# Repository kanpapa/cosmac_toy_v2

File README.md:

# COSMAC Toy Computer Version 2

[COSMAC Toy Computer](https://github.com/kanpapa/cosmac_toy)は「トラ技別冊 つくるシリーズ7 手作りコンピュータ入門」（1981年5月初版）を参考にして、COSMAC CPUボードやプログラムローダーや実験回路をコンパクトな基板にまとめて製作したものです。  
ROMは搭載されておらず、トグルスイッチでRAMにプログラムを書き込んで実行できます。  
16進キーボードを使ったことはあるけど、トグルスイッチを使ってプログラムを動かしてみたいという方の願いを叶えようという思いで作られたシンプルなボードです。モニタプログラムなどの助けを借りずに、トグルスイッチでメモリを直接書き換えてプログラムを実行するといった一連の操作を体験できます。

最初に製作したCOSMAC TOYは1980年代の当時の環境に近づけるべく可能な限り書籍を忠実に再現することを第一に製作しましたので、やや入手が容易ではないパーツも含まれていました。  
このため、実機を使って[COSMACマイコン](https://kanpapa.com/cosmac/cosmac-cpu)の基本的な動きとトグルスイッチによるブートストラップを容易に体験いただけるようにVersion 2として見直しを行いました。

さらに高度なプログラミングを行いたい場合は、モニタが搭載された[SBC1802](https://vintagechips.wordpress.com/2021/04/13/sbc1802fixed/)や[MemberShip Card](https://www.sunrise-ev.com/1802.htm)などの利用をおすすめします。

## Version 2での変更点

* CPUボードとローダーボードを1枚の基板にまとめ、さらに製作を容易にしました。
* メモリを書き込み禁止にするトグルスイッチを追加することで、メモリ内容の読み出しや正しく手順を踏めばメモリの修正も行えるようになりました。
* 600milのS-RAMを使用できるようにしました。これにより600milの6264ALPやDIP変換基板に実装したフラットパッケージのS-RAMも使用できます。
* COSMAC CPUの全ピンにアクセスできるようにピンソケット用のパターンを併設しました。
* Q出力がLEDでモニタできるようになりました。基板単体でQ出力の確認ができます。
* COSMAC CPUとS-RAMを除きすべて秋月電子さんで購入できるパーツとしました。
* USB-C電源コネクタを追加しました。(Rev.0.3)
* 入力トグルスイッチと出力LEDにおいて上位4ビットと下位4ビットの間隔を少し空けました。(Rev.0.3)

## スペック

* CPU: COSMAC CDP1802
* RAM: 256byte
* ROM: 無し
* CLOCK: 約400kHz
* I/O: バスLED, Q-LED, バス設定トグルスイッチ, モード設定トグルスイッチ
* 電源: 5V 標準DCジャック(センタープラス)、USB-C電源(Rev.0.3)
* メモリバックアップバッテリー: CR2032 3V
* サイズ: 95mmX72mm
* 重さ: 約89g（全パーツ実装時）

## 外観
Rev.0.3  
  
[Rev.0.2](/docs/images/cosmac_toy_v2-rev02-600mil.jpg)  
[Rev.0.1](/docs/images/cosmac_toy_v2-rev01-prototype.jpg)  

## 特徴

* 入手が容易なパーツを使い、回路を極力簡素化することで必要なパーツ数を減らしています。専用基板も表面実装パーツは使用せずに製作しやすくしています。
* トグルスイッチで直接メモリに書き込むため、ROMライタなどの開発ツールは不要です。
* COSMAC CPUの全ピンにアクセスできるようにピンソケットを併設しています。CPUバスやQ出力やEF1~4入力などのアクセスはここから行ってください。
* メモリは6264を使用していますが、実際に使えるのは256バイトだけです。これはトグルスイッチで正確に手入力できるのは256バイトが限界と思われるため、アドレスバスを簡略化したためです。
* S-RAMは簡易的なバッテリバックアップが行えます。SW11をSTBYにするとメモリをスタンバイ状態にし、バッテリーで内容が保持されます。
* 8つのLEDはバスの信号をラッチしてバスの状態を表示することができます。
* 右上の3つのトグルスイッチで、CPUの動作モードを設定したあとに、DMA INにつながっているプッシュスイッチを押すことで、トグルスイッチで設定した値をメモリに書き込むことができます。ROにすることでメモリに書き込まずメモリの状態を確認することもできます。
* トグルスイッチはバスの信号を直接0/1に設定します。通常はバスバッファを介しますが、シンプルな回路にするために省略しています。
* Q出力はLEDが接続されています。  
* COSMAC CPUのクロックはCR発振なのでCRの値を変えることで周波数を調整できます。
* 本基板のサイズは秋月電子のB基板に合わせました。

## 基本的な操作方法

* [Quick start guide](/docs/cosmac_toy_v2_quick_start_guide.pdf)も合わせてご覧ください。

    UP    トグルスイッチを上側に倒します  
    DOWN  トグルスイッチを下側に倒します  
     ↓  　トグルスイッチの状態をそのまま維持します。（変更しない）  
     ー   トグルスイッチの状態は任意です。（上側でも下側でも良い）  

1. メモリ書き込み

    |Step|SW9|SW10|SW12|操作内容|
    |---|----|---|----|----|
    |1	|UP|DOWN|-|CPUを初期状態(P, X, R(0)を0)にする(RESETモード)|	
    |2	|↓|↓|UP|メモリ書き込み許可|
    |3	|DOWN|↓|↓|メモリロード状態にする(LOADモード)|
    |4	|| | |トグルスイッチでメモリに書き込む値を設定→DMAINを押す（これを繰り返す） |

1. メモリ読み出し
    |Step|SW9|SW10|SW12|操作内容|
    |---|---|----|----|----|
    |1	|UP|DOWN|-|CPUを初期状態にする(RESETモード)|
    |2  |↓|↓|DOWN|メモリ書き込み禁止|
	|3  |DOWN|↓|↓|メモリロード状態にする(LOADモード)|	
	|4  | | | |DMAINボタンを押すとメモリの内容が表示される（これを繰り返す）|		

1. プログラム実行
    |Step|SW9|SW10|SW12|操作内容|
    |---|----|---|----|----|
    |1|UP|DOWN|-|CPUを初期状態にする(RESETモード)|
    |2|↓|↓|UP|メモリ書き込み許可(メモリに書き込む処理があるプログラムの場合)|	
	|3|↓|UP|↓|プログラム実行状態にする(RUNモード)|

1. プログラム一時停止
    |Step|SW9|SW10|SW12|操作内容|
    |---|---|---|---|---|
	|1|DOWN|UP|-|プログラム実行を一時停止する(PAUSEモード)|
	|2|UP|↓|- |プログラム実行状態にする(RUNモード)|

1. メモリバックアップ状態〜通常状態への切替
    |Step|SW9|SW10|SW12|SW11|操作内容|
    |---|---|---|---|---|---|
    |1|DOWN|UP|-|RUN|プログラムを一時停止する(PAUSEモード)|
    |2|↓|↓|DOWN|↓|メモリ書き込み禁止|
    |3|↓|↓|↓|STBY|RAMをスタンバイモードにする|
    |4|↓|↓|↓|↓|電源を切断|
    |5|DOWN|UP|DOWN|STBY|PAUSEモード+メモリ書き込み禁止になっていることを確認|
    |6|↓|↓|↓|↓|電源を投入|
    |7|↓|↓|↓|RUN|RAMをノーマルモードにする|

※メモリバックアップを行わない場合はリチウム電池は抜いておいてください。電源が供給されない状態でSW11がRUNのままだと放電してしまいます。

## ハードウェア

- [回路図](/schematics/)
- [部品表](/bom/)
- [KiCadデータ](/kicad/)
- [ガーバーデータ](/gerber/)
- [組み立て手順例](/docs/Assembly_instruction/)
- 組み立て時の注意事項  
    - 部品表に記載されているLEDと異なるLEDを使用する場合は、RN3 2.2KΩの集合抵抗では眩しすぎる場合もありますので、丸ピンソケットを利用して集合抵抗を交換調整できるようにしておくことをお勧めします。

## ソフトウェア
 
- [サンプルアプリケーション](/programs/)

## 補足情報

- [COSMAC研究会](https://kanpapa.com/cosmac/)に関連記事をまとめています。

## 参考・引用文献

- トランジスタ技術別冊 つくるシリーズ７ 手作りコンピュータ入門 CQ出版社, 1981
- [KiCad 8 入門実習テキスト『KiCad Basics for 8.0』Kosaka.Lab.出版掛](https://kosakalab.booth.pm/items/5554691)
- [intersil CDP1802AC/3データシート](https://www.renesas.com/jp/ja/www/doc/datasheet/cdp1802ac-3.pdf)
- [SB-Assembler](https://www.sbprojects.net/sbasm/)
- [COSMAC ELF - RCA CDP1802 Computing](http://www.cosmacelf.com/)
- [Compute II Issue 3: The 1802 Instruction Set](https://www.atarimagazines.com/computeii/issue3/page52.php)
- [The 1802 Membership Card](http://www.sunrise-ev.com/1802.htm)

## 利用上の注意

本サイトに掲載している回路、技術、プログラムなどは無保証です。  
これらの利用によって発生したトラブルには責任を負いかねます。自己責任にてご利用ください。  
KiCADデータおよびガーバーデータはCC BY-SA 4.0 (Copyright (C) 2024 Kazuhiro Ouchi)です。  
サンプルプログラムはMITライセンスです。

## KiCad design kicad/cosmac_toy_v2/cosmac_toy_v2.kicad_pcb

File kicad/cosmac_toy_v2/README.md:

# COSMAC TOY V2 KiCad project

COSMAC TOY V2の基板のKiCADデータです。

以下に公開されているフットプリントを使用させていただきました。

* USB Type-Cコネクター 電源供給用	A295-CTRPB-1:A295-CTRPB-1  
https://github.com/21km43/A295-CTRPB-1_KiCAD  
Copyright (c) 2023 Koki Mizumoto

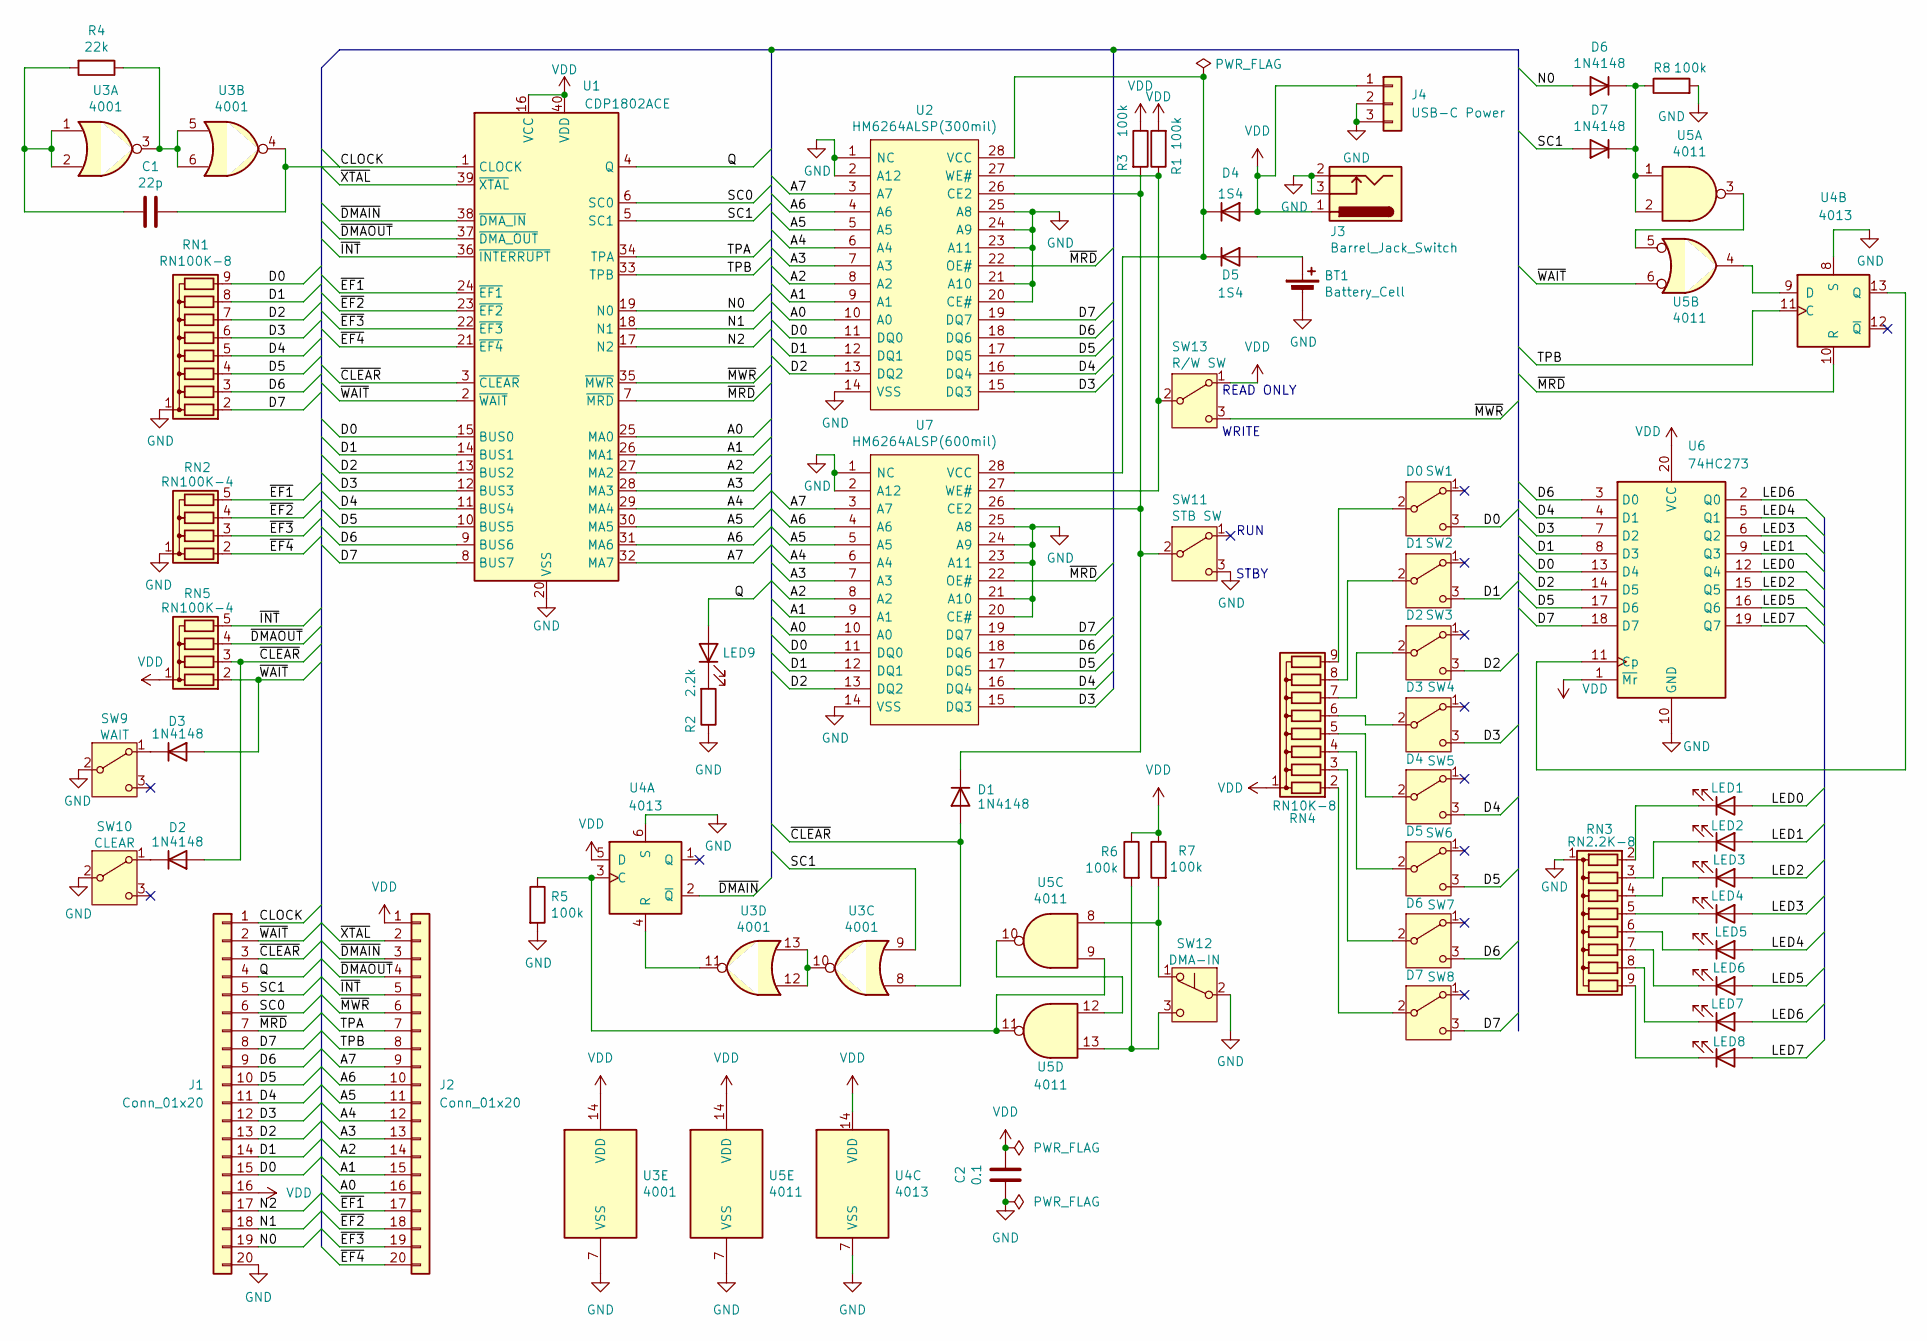
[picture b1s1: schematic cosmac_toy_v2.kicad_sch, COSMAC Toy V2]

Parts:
BT1: Battery_Cell; CH243-2032CF
C1: 22p; C_Disc_D4.7mm_W2.5mm_P5.00mm
C2: 0.1; C_Disc_D4.7mm_W2.5mm_P5.00mm
D1, D2, D3, D6, D7: 1N4148; D_DO-35_SOD27_P7.62mm_Horizontal
D4, D5: 1S4; D_A-405_P7.62mm_Horizontal
J1, J2: Conn_01x20; PinSocket_1x20_P2.54mm_Vertical
J3: Barrel_Jack_Switch; BarrelJack_Horizontal
J4: USB-C Power; A295-CTRPB-1
LED1, LED2, LED3, LED4, LED5, LED6, LED7, LED8: DATA_LED; LED_D3.0mm
LED9: Q; LED_D3.0mm
R1, R3, R5, R6, R7, R8: 100k; R_Axial_DIN0207_L6.3mm_D2.5mm_P7.62mm_Horizontal
R2: 2.2k; R_Axial_DIN0207_L6.3mm_D2.5mm_P7.62mm_Horizontal
R4: 22k; R_Axial_DIN0207_L6.3mm_D2.5mm_P7.62mm_Horizontal
RN1: RN100K-8; R_Array_SIP9
RN2, RN5: RN100K-4; R_Array_SIP5
RN3: RN2.2K-8; R_Array_SIP9
RN4: RN10K-8; R_Array_SIP9
SW1: D0; SW_Toggle_P2.54mm_Vertical
SW2: D1; SW_Toggle_P2.54mm_Vertical
SW3: D2; SW_Toggle_P2.54mm_Vertical
SW4: D3; SW_Toggle_P2.54mm_Vertical
SW5: D4; SW_Toggle_P2.54mm_Vertical
SW6: D5; SW_Toggle_P2.54mm_Vertical
SW7: D6; SW_Toggle_P2.54mm_Vertical
SW8: D7; SW_Toggle_P2.54mm_Vertical
SW9: WAIT; SW_Toggle_P2.54mm_Vertical
SW10: CLEAR; SW_Toggle_P2.54mm_Vertical
SW11: STB SW; PinHeader_1x03_P2.54mm_Vertical
SW12: DMA-IN; PushSwitch
SW13: R/W SW; SW_Toggle_P2.54mm_Vertical
U1: CDP1802ACE; DIP-40_W15.24mm_Socket
U2: HM6264ALSP(300mil); DIP-28_W7.62mm_Socket
U3: 4001; DIP-14_W7.62mm
U4: 4013; DIP-14_W7.62mm
U5: 4011; DIP-14_W7.62mm
U6: 74HC273; DIP-20_W7.62mm
U7: HM6264ALSP(600mil); DIP-28_W15.24mm_Socket

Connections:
/A0: J2.16, U1.25 (MA0), U2.10 (A0), U7.10 (A0)
/A1: J2.15, U1.26 (MA1), U2.9 (A1), U7.9 (A1)
/A2: J2.14, U1.27 (MA2), U2.8 (A2), U7.8 (A2)
/A3: J2.13, U1.28 (MA3), U2.7 (A3), U7.7 (A3)
/A4: J2.12, U1.29 (MA4), U2.6 (A4), U7.6 (A4)
/A5: J2.11, U1.30 (MA5), U2.5 (A5), U7.5 (A5)
/A6: J2.10, U1.31 (MA6), U2.4 (A6), U7.4 (A6)
/A7: J2.9, U1.32 (MA7), U2.3 (A7), U7.3 (A7)
/CLOCK: C1.2, J1.1, U1.1 (CLOCK), U3.4
/D0: J1.15, RN1.9 (R8), SW1.3 (C), U1.15 (BUS0), U2.11 (DQ0), U6.13 (D4), U7.11 (DQ0)
/D1: J1.14, RN1.8 (R7), SW2.3 (C), U1.14 (BUS1), U2.12 (DQ1), U6.8 (D3), U7.12 (DQ1)
/D2: J1.13, RN1.7 (R6), SW3.3 (C), U1.13 (BUS2), U2.13 (DQ2), U6.14 (D5), U7.13 (DQ2)
/D3: J1.12, RN1.6 (R5), SW4.3 (C), U1.12 (BUS3), U2.15 (DQ3), U6.7 (D2), U7.15 (DQ3)
/D4: J1.11, RN1.5 (R4), SW5.3 (C), U1.11 (BUS4), U2.16 (DQ4), U6.4 (D1), U7.16 (DQ4)
/D5: J1.10, RN1.4 (R3), SW6.3 (C), U1.10 (BUS5), U2.17 (DQ5), U6.17 (D6), U7.17 (DQ5)
/D6: J1.9, RN1.3 (R2), SW7.3 (C), U1.9 (BUS6), U2.18 (DQ6), U6.3 (D0), U7.18 (DQ6)
/D7: J1.8, RN1.2 (R1), SW8.3 (C), U1.8 (BUS7), U2.19 (DQ7), U6.18 (D7), U7.19 (DQ7)
/LED0: LED1.2 (A), U6.12 (Q4)
/LED1: LED2.2 (A), U6.9 (Q3)
/LED2: LED3.2 (A), U6.15 (Q5)
/LED3: LED4.2 (A), U6.6 (Q2)
/LED4: LED5.2 (A), U6.5 (Q1)
/LED5: LED6.2 (A), U6.16 (Q6)
/LED6: LED7.2 (A), U6.2 (Q0)
/LED7: LED8.2 (A), U6.19 (Q7)
/N0: D6.2 (A), J1.19, U1.19 (N0)
/N1: J1.18, U1.18 (N1)
/N2: J1.17, U1.17 (N2)
/Q: J1.4, LED9.2 (A), U1.4 (Q)
/SC0: J1.6, U1.6 (SC0)
/SC1: D7.2 (A), J1.5, U1.5 (SC1), U3.9
/TPA: J2.7, U1.34 (TPA)
/TPB: J2.8, U1.33 (TPB), U4.11 (C)
/~CLEAR: D1.2 (A), D2.2 (A), J1.3, RN5.3 (R2), U1.3 (~CLEAR), U3.8
/~DMAIN: J2.3, U1.38 (~DMA_IN), U4.2 (~Q)
/~DMAOUT: J2.4, RN5.4 (R3), U1.37 (~DMA_OUT)
/~EF1: J2.17, RN2.5 (R4), U1.24 (~EF1)
/~EF2: J2.18, RN2.4 (R3), U1.23 (~EF2)
/~EF3: J2.19, RN2.3 (R2), U1.22 (~EF3)
/~EF4: J2.20, RN2.2 (R1), U1.21 (~EF4)
/~INT: J2.5, RN5.5 (R4), U1.36 (~INTERRUPT)
/~MRD: J1.7, U1.7 (~MRD), U2.22 (OE#), U4.10 (R), U7.22 (OE#)
/~MWR: J2.6, SW13.3 (C), U1.35 (~MWR)
/~WAIT: D3.2 (A), J1.2, RN5.2 (R1), U1.2 (~WAIT), U5.6
/~XTAL: J2.2, U1.39 (~XTAL)
GND: BT1.2 (-), C2.2, J1.20, J3.2, J3.3, J4.2, J4.3, R2.1, R5.2, R8.2, RN1.1 (common), RN2.1 (common), RN3.1 (common), SW9.2 (B), SW10.2 (B), SW11.3 (C), SW12.2 (B), U1.20 (VSS), U2.1 (NC), U2.2 (A12), U2.14 (VSS), U2.20 (CE#), U2.21 (A10), U2.23 (A11), U2.24 (A9), U2.25 (A8), U3.7 (VSS), U4.6 (S), U4.7 (VSS), U4.8 (S), U5.7 (VSS), U6.10 (GND), U7.1 (NC), U7.2 (A12), U7.14 (VSS), U7.20 (CE#), U7.21 (A10), U7.23 (A11), U7.24 (A9), U7.25 (A8)
unnamed: BT1.1 (+), D5.2 (A)
unnamed: C1.1, R4.2, U3.1, U3.2
unnamed: D1.1 (K), R3.2, SW11.2 (B), U2.26 (CE2), U7.26 (CE2)
unnamed: D2.1 (K), SW10.1 (A)
unnamed: D3.1 (K), SW9.1 (A)
unnamed: D4.1 (K), D5.1 (K), U2.28 (VCC), U7.28 (VCC)
unnamed: D6.1 (K), D7.1 (K), R8.1, U5.1, U5.2
unnamed: LED1.1 (K), RN3.2 (R1)
unnamed: LED2.1 (K), RN3.3 (R2)
unnamed: LED3.1 (K), RN3.4 (R3)
unnamed: LED4.1 (K), RN3.5 (R4)
unnamed: LED5.1 (K), RN3.6 (R5)
unnamed: LED6.1 (K), RN3.7 (R6)
unnamed: LED7.1 (K), RN3.8 (R7)
unnamed: LED8.1 (K), RN3.9 (R8)
unnamed: LED9.1 (K), R2.2
unnamed: R4.1, U3.3, U3.5, U3.6
unnamed: RN4.2 (R1), SW8.2 (B)
unnamed: RN4.3 (R2), SW7.2 (B)
unnamed: RN4.4 (R3), SW6.2 (B)
unnamed: RN4.5 (R4), SW5.2 (B)
unnamed: RN4.6 (R5), SW4.2 (B)
unnamed: RN4.7 (R6), SW3.2 (B)
unnamed: RN4.8 (R7), SW2.2 (B)
unnamed: RN4.9 (R8), SW1.2 (B)
unnamed: R7.2, SW12.1 (A), U5.8
unnamed: R6.2, SW12.3 (C), U5.13
unnamed: R1.1, SW13.2 (B), U2.27 (WE#), U7.27 (WE#)
unnamed: U3.10, U3.12, U3.13
unnamed: R5.1, U4.3 (C), U5.9, U5.11
unnamed: U3.11, U4.4 (R)
unnamed: U4.9 (D), U5.4
unnamed: U4.13 (Q), U6.11 (Cp)
unnamed: U5.3, U5.5
unnamed: U5.10, U5.12
VDD: C2.1, D4.2 (A), J1.16, J2.1, J3.1, J4.1, R1.2, R3.1, R6.1, R7.1, RN4.1 (common), RN5.1 (common), SW13.1 (A), U1.16 (VCC), U1.40 (VDD), U3.14 (VDD), U4.5 (D), U4.14 (VDD), U5.14 (VDD), U6.1 (~Mr), U6.20 (VCC)

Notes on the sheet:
RUN
STBY
WRITE
READ ONLY

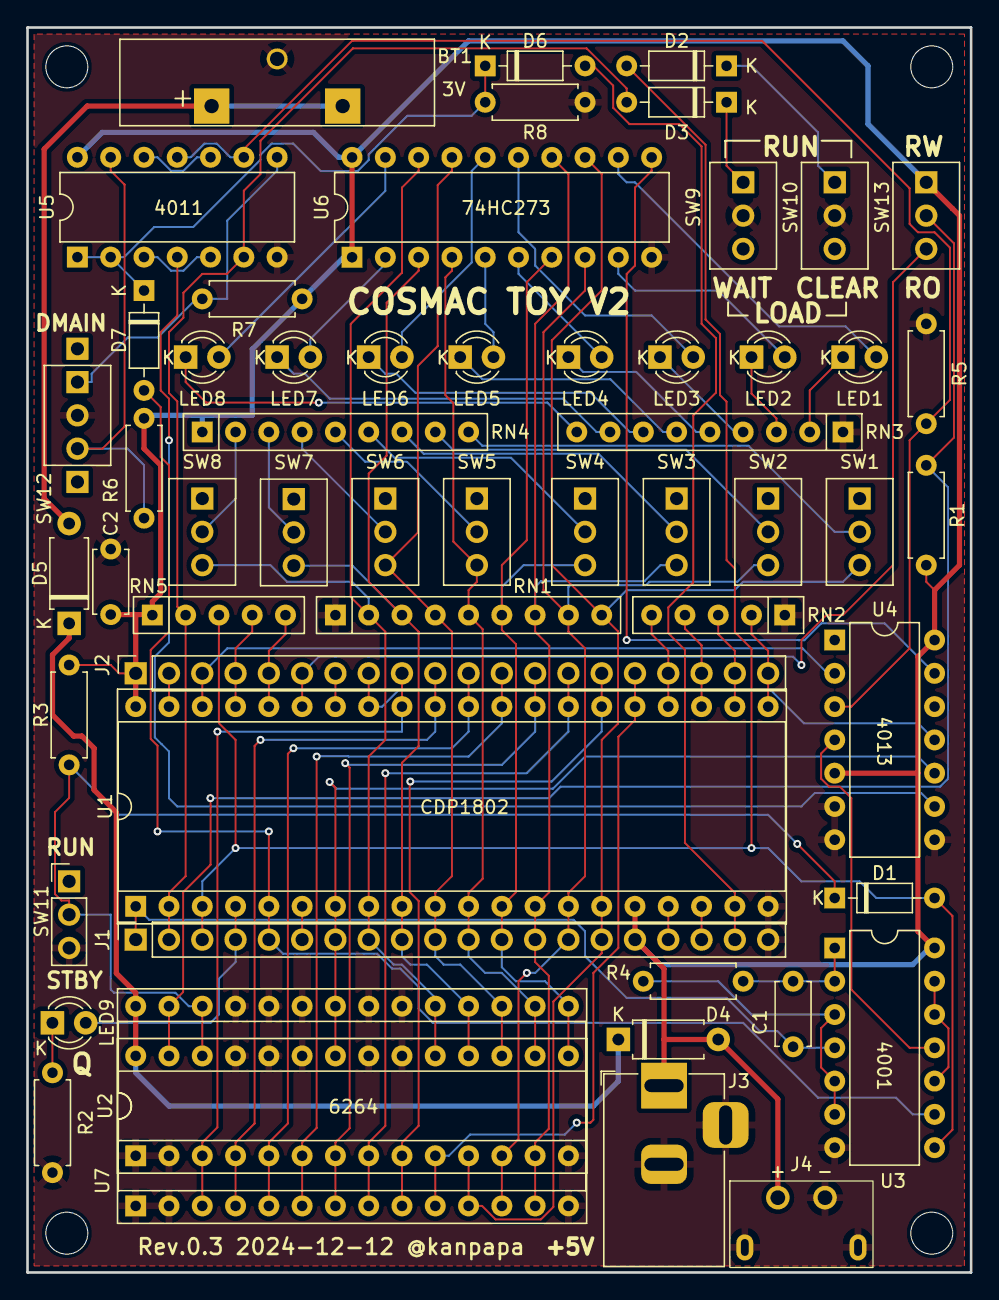
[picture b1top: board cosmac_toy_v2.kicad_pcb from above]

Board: 2 copper layers, 72.0 x 95.0 mm, 60 parts (0 on the bottom side), 82 nets.

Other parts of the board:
MH1, MH2, MH3, MH4: MountingHole_3.2mm_M3

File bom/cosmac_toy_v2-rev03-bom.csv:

Reference,Value,Datasheet,Footprint,Qty,参考入手先,秋月電子販売コード,参考価格,計,
BT1,Battery_Cell,ボタン電池基板取付用ホルダー CR2032用(縦型),Switch_Toggle:CH243-2032CF,1,秋月電子,102019,80,80,
C1,22p,積層セラミックコンデンサー 22pF50V C0G 5mm,Capacitor_THT:C_Disc_D4.7mm_W2.5mm_P5.00mm,1,秋月電子,108094,130,13,10個入
C2,0.1uF,積層セラミックコンデンサー 0.1μF100V X7R 5mmピッチ,Capacitor_THT:C_Disc_D4.7mm_W2.5mm_P5.00mm,1,秋月電子,115927,120,12,10個入
"D1,D2,D3,D6,D7",1N4148,汎用小信号高速スイッチング・ダイオード 1N4148 100V200mA,Diode_THT:D_DO-35_SOD27_P7.62mm_Horizontal,5,秋月電子,100941,150,15,50本入り
"D4,D5",1S4,整流用ショットキーダイオード 40V1A 1S4,Diode_THT:D_A-405_P7.62mm_Horizontal,2,秋月電子,100127,20,40,
"J1,J2",Conn_01x20,ピンソケット (メス) 1×20 (20P),Connector_PinSocket_2.54mm:PinSocket_1x20_P2.54mm_Vertical,2,秋月電子,103077,50,100,
J3,Barrel_Jack_Switch,2.1mm標準DCジャック(4A) 基板取付用 MJ-179PH,Connector_BarrelJack:BarrelJack_Horizontal,1,秋月電子,106568,40,40,J3とJ4はどちらかを選択
J4,USB-C Power,USB Type-Cコネクター 電源供給用,A295-CTRPB-1:A295-CTRPB-1,1,秋月電子,116895,40,40,https://github.com/21km43/A295-CTRPB-1_KiCAD
"LED1,LED2,LED3,LED4,LED5,LED6,LED7,LED8",DATA_LED,3mm赤色LED 625nm 70度 OSR5JA3Z74A,LED_THT:LED_D3.0mm,8,秋月電子,111577,10,80,10個入
LED9,Q,3mm赤色LED 625nm 70度 OSR5JA3Z74A,LED_THT:LED_D3.0mm,1,秋月電子,111577,10,10,
"R1,R3,R5,R6,R7,R8",100k,カーボン抵抗(炭素皮膜抵抗) 1/4W100kΩ,Resistor_THT:R_Axial_DIN0207_L6.3mm_D2.5mm_P7.62mm_Horizontal,6,秋月電子,125104,130,7.8,100本入
R4,22k,カーボン抵抗(炭素皮膜抵抗) 1/4W22kΩ,Resistor_THT:R_Axial_DIN0207_L6.3mm_D2.5mm_P7.62mm_Horizontal,1,秋月電子,125223,130,1,
R2,2.2k,カーボン抵抗(炭素皮膜抵抗) 1/4W2.2kΩ,Resistor_THT:R_Axial_DIN0207_L6.3mm_D2.5mm_P7.62mm_Horizontal,1,秋月電子,125222,100,1,100本入
RN1,RN100K-8,集合抵抗 8素子 100kΩ,Resistor_THT:R_Array_SIP9,1,秋月電子,114228,25,25,
RN2,RN100K-4,集合抵抗 4素子 100kΩ,Resistor_THT:R_Array_SIP5,1,秋月電子,114246,15,15,
RN3,RN2.2K-8,集合抵抗 8素子 2.2kΩ,Resistor_THT:R_Array_SIP9,1,秋月電子,113915,30,30,
RN4,RN10K-8,集合抵抗 8素子 10kΩ,Resistor_THT:R_Array_SIP9,1,秋月電子,111910,40,40,
RN5,RN100K-4,集合抵抗 4素子 100kΩ,Resistor_THT:R_Array_SIP5,1,秋月電子,114246,15,15,
SW1,D0,基板用小型3Pトグルスイッチ 1回路2接点,Switch_Toggle:SW_Toggle_P2.54mm_Vertical,1,秋月電子,102399,130,130,
SW2,D1,基板用小型3Pトグルスイッチ 1回路2接点,Switch_Toggle:SW_Toggle_P2.54mm_Vertical,1,秋月電子,102399,130,130,
SW3,D2,基板用小型3Pトグルスイッチ 1回路2接点,Switch_Toggle:SW_Toggle_P2.54mm_Vertical,1,秋月電子,102399,130,130,
SW4,D3,基板用小型3Pトグルスイッチ 1回路2接点,Switch_Toggle:SW_Toggle_P2.54mm_Vertical,1,秋月電子,102399,130,130,
SW5,D4,基板用小型3Pトグルスイッチ 1回路2接点,Switch_Toggle:SW_Toggle_P2.54mm_Vertical,1,秋月電子,102399,130,130,
SW6,D5,基板用小型3Pトグルスイッチ 1回路2接点,Switch_Toggle:SW_Toggle_P2.54mm_Vertical,1,秋月電子,102399,130,130,
SW7,D6,基板用小型3Pトグルスイッチ 1回路2接点,Switch_Toggle:SW_Toggle_P2.54mm_Vertical,1,秋月電子,102399,130,130,
SW8,D7,基板用小型3Pトグルスイッチ 1回路2接点,Switch_Toggle:SW_Toggle_P2.54mm_Vertical,1,秋月電子,102399,130,130,
SW9,WAIT,基板用小型3Pトグルスイッチ 1回路2接点,Switch_Toggle:SW_Toggle_P2.54mm_Vertical,1,秋月電子,102399,130,130,
SW10,CLEAR,基板用小型3Pトグルスイッチ 1回路2接点,Switch_Toggle:SW_Toggle_P2.54mm_Vertical,1,秋月電子,102399,130,130,
SW11,STB SW,スライドスイッチ 1回路2接点 基板用,Connector_PinHeader_2.54mm:PinHeader_1x03_P2.54mm_Vertical,1,秋月電子,115707,20,20,
SW12,DMA-IN,押しボタンスイッチ(赤),Switch_Toggle:PushSwitch,1,秋月電子,104366,180,180,
SW13,R/W SW,基板用小型3Pトグルスイッチ 1回路2接点,Switch_Toggle:SW_Toggle_P2.54mm_Vertical,1,秋月電子,102399,130,130,
U1,CDP1802ACE,http://www.cosmacelf.com/publications/data-sheets/cdp1802.pdf,Package_DIP:DIP-40_W15.24mm_Socket,1,オレンジピコ,,746,746,
U2,HM6264ALSP(300mil),,Package_DIP:DIP-28_W7.62mm_Socket,1,ー,,,,U2とU7はどちらかを選択
U3,4001,4回路2入力NOR TC4001BP,Package_DIP:DIP-14_W7.62mm,1,秋月電子,110911,50,50,
U4,4013,2回路Dフリップフロップ TC4013BP,Package_DIP:DIP-14_W7.62mm,1,秋月電子,114210,40,40,
U5,4011,4回路2入力NAND TC4011BP,Package_DIP:DIP-14_W7.62mm,1,秋月電子,113729,40,40,
U6,74HC273,Dフリップフロップ(D-FF) TC74HC273AP,Package_DIP:DIP-20_W7.62mm,1,秋月電子,115412,70,70,
U7,HM6264ALP(600mil),,Package_DIP:DIP-28_W15.24mm_Socket,1,若松通商,,850,850,U2とU7はどちらかを選択
,,専用基板,,1,JLCPCB,,100,100,5枚で約500円
,,丸ピンICソケット (40P),,1,秋月電子,100034,90,90,
,,丸ピンICソケット (28P) 300mil,,1,秋月電子,101339,70,70,
,,ICソケット (20P),,1,秋月電子,100009,170,17,10個入
,,ICソケット (14P),,3,秋月電子,100006,120,36,10個入
,,丸ピンIC用ソケット (シングル14P) 1×14,,2,秋月電子,103470,50,100,
,,,,,,,,4403.8,
,,,,,,,,,
以下64Kメモリが入手できない場合の代替用,,,,,,,,,
,,SRAM 64Kb LC3564SM-70,,1,,114234,100,100,在庫限り
,,SOP28ピン(1.27mm)DIP変換基板 金フラッシュ,,1,,104603,70,70,
,,丸ピンIC用連結ソケット 1×14 MH-1X14-L2：,,2,,116982,70,140,
,,,,,,,,,
,,バッテリバックアップ非対応ですが、256Kメモリも使えるはず。,,,,,,,

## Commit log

2024-12-08 1st commit
2024-12-08 使用方法の書き方を修正
2024-12-08 メモリ書き込み禁止スイッチについて補足を追加
2024-12-08 回路図を追加
2024-12-08 README.mdの章立てを修正
2024-12-08 BOMの追加とファイル名見直し
2024-12-08 推敲結果を反映
2024-12-08 行間調整
2024-12-08 操作方法の記載内容を見直し
2024-12-08 fixed typo
2024-12-08 Added programs
2024-12-09 Added sw1.asm
2024-12-09 Updated README.md for sw1.asm
2024-12-09 Added 06_blink1
2024-12-09 Updated 06_blink1
2024-12-09 Added images
2024-12-09 Added programs README
2024-12-09 Added sw1_sch.png
2024-12-09 Updated sw1 README
2024-12-10 サンプルプログラムOSC1で実行中の写真を追加
2024-12-10 counter1, counter2 にファイル名を変更し、画像を追加
2024-12-10 改行を修正
2024-12-10 再度改行を修正
2024-12-10 osc1のREDAMEに使用する命令を追記
2024-12-10 URLを修正
2024-12-10 Update programs README
2024-12-10 fixed counter2
2024-12-10 fixe typo
2024-12-10 サンプルプログラムの加算結果の写真を追加
2024-12-10 sw1とblink1に動画を追加
2024-12-10 文面の調整
2024-12-10 added link
2024-12-10 Added KICad project data and gerber data
2024-12-10 配布不要なファイルの削除
2024-12-11 参考入手先の記載漏れがあったので修正
2024-12-11 メモリバックアップ状態〜通常状態への切り替え手順の誤記を修正
2024-12-22 Added rev.0.3 images
2024-12-22 Fixed imagesFixed images
2024-12-23 Added KiCad project Rev.0.3
2024-12-24 Added BOM for Rev.0.3
2024-12-24 KiCad ProjectのREADMEを追加
2024-12-24 Updated README for Rev.0.3
2024-12-24 Rev.0.3の回路図を追加
2024-12-24 Rev.0.3 の回路図を追加
2024-12-24 不要なファイルを削除
2024-12-24 Rev.0.1の写真を追加
2024-12-24 リチウム電池の取り扱いについて注意事項を追記しました
2024-12-24 Rev.0.3の回路図を修正
2024-12-26 Added POV sample program
2024-12-26 Updated POV readme
2024-12-26 Updated README for 07_pov1
2024-12-26 Fixed pov1 asm
2024-12-27 使用するLEDによってはRN3を調整する必要があることを明記しました。
2024-12-27 LEDを10個入りパックの型番に変更
2024-12-27 コメントを追加
2024-12-27 同じ型番のものは統合
2024-12-27 単価を修正
2024-12-27 BOMで同一型番のものは集約
2024-12-27 単価のミスを修正
2024-12-28 合計の誤りを修正
2024-12-28 入手先の記載漏れを修正
2024-12-28 電源用USB−Cコネクタが入荷未定となっているので代替品を追記
2024-12-31 Added Serial binary loader
2024-12-31 Added source and assemble list
2024-12-31 EF3が負論理であることを回路図に明記
2024-12-31 Resized image
2025-01-02 Added Assembly instructions
2025-01-02 Updated assembly readme
2025-01-02 Updated Assembly instructions
2025-01-29 Updated Quick start guide
2025-01-29 Added quick start guide
2025-01-29 組み立て手順書に回路図と部品表をリンク
2025-01-29 Update quick start guide
2025-02-06 組み立て手順書にパーツの定格等を追加
